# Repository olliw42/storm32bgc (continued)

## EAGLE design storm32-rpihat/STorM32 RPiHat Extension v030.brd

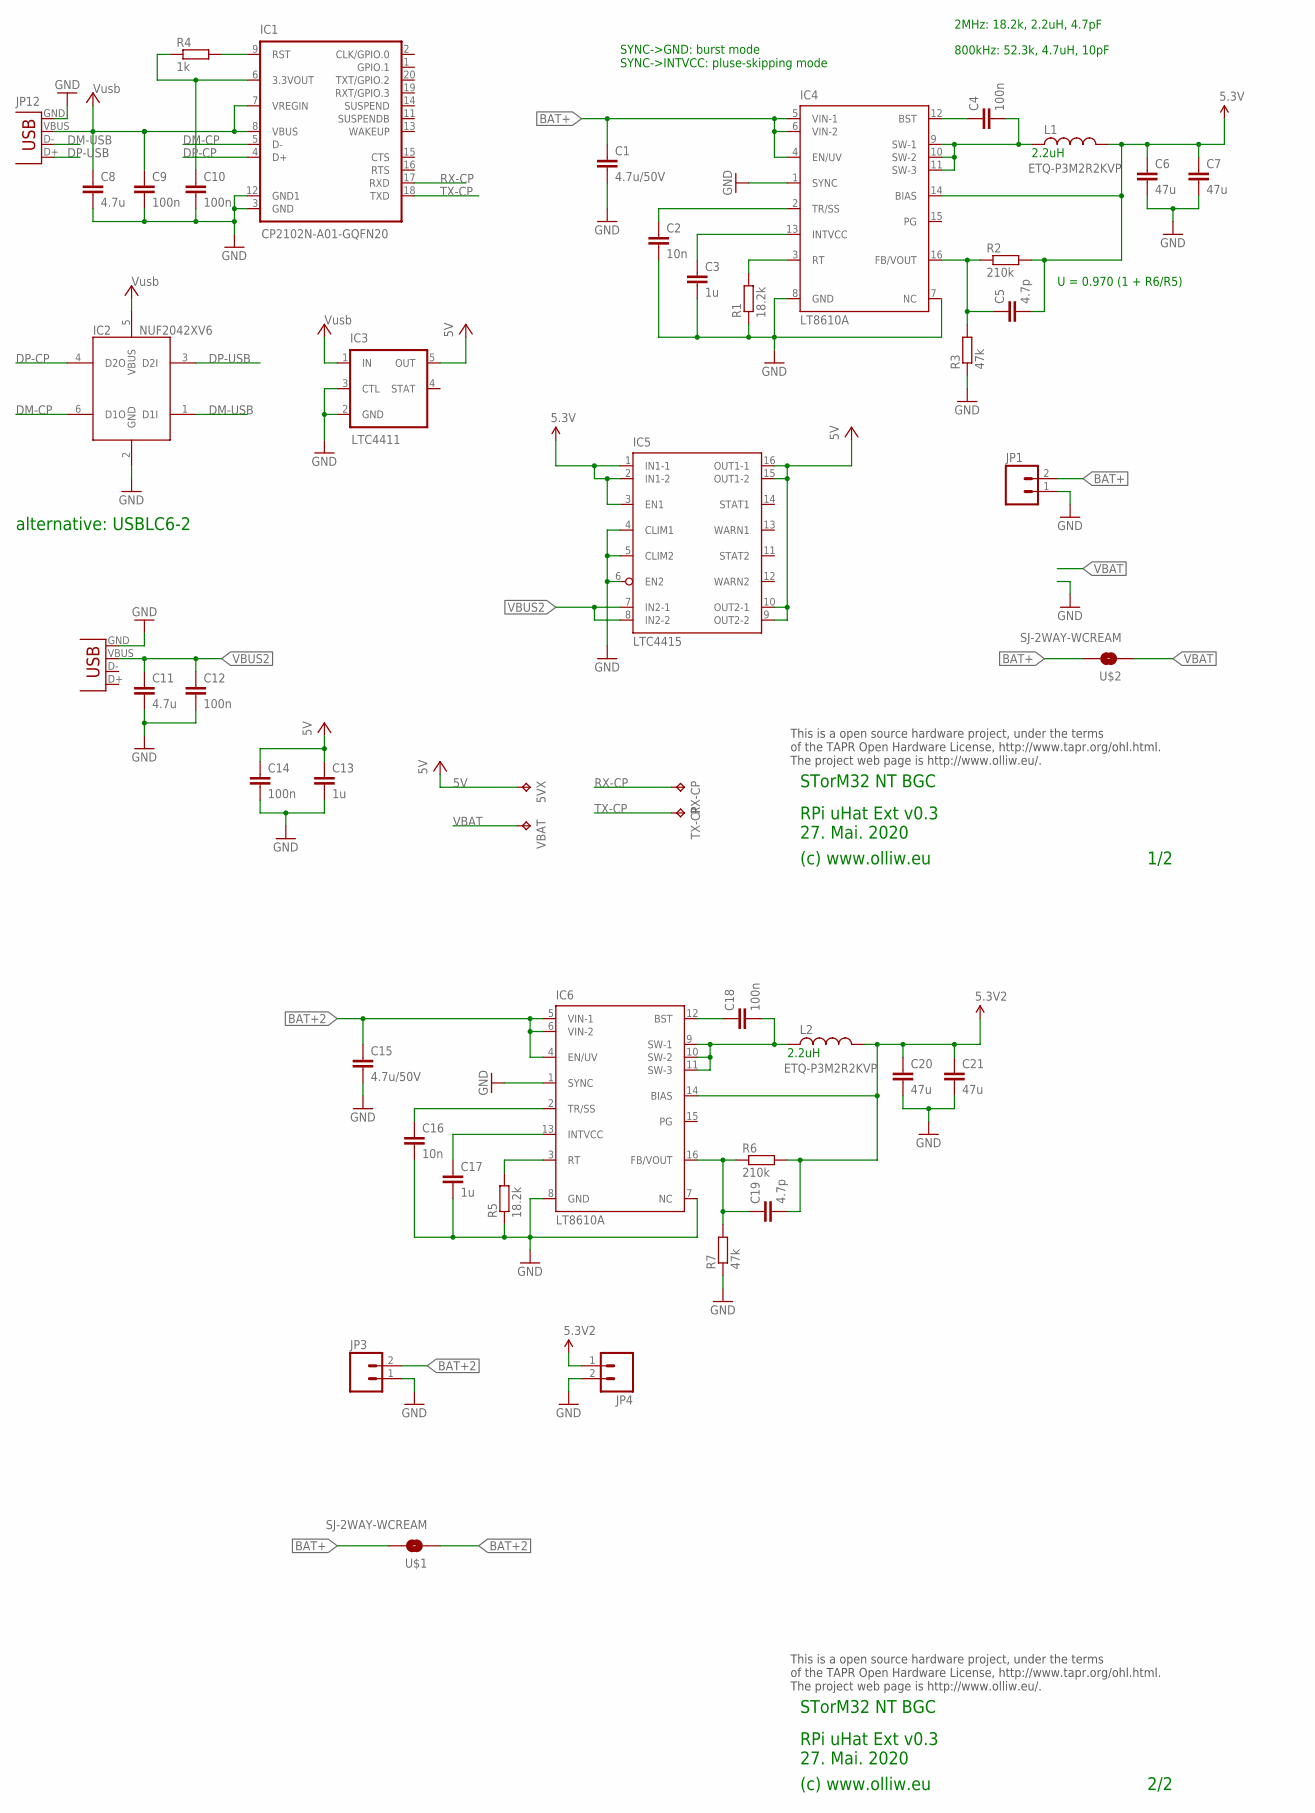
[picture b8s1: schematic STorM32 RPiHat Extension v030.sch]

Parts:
5VX: TPB1,27; B1,27
C1, C15: 4.7u/50V; C1206
C2, C16: 10n; C0603K
C3, C17: 1u; C0603K
C4, C18: 100n; C0603K
C5, C19: 4.7p; C0603K
C6, C7, C20, C21: 47u; C1210
C8, C11: 4.7u; C0603
C9, C10, C12, C14: 100n; C0402
C13: 1u; C0603
IC1: CP2102N-A01-GQFN20; QFN20-CP2102N
IC2: NUF2042XV6; SOT563-6
IC3: LTC4411; SOT23-5-SPARKFUN
IC4, IC6: LT8610A; MSOP16
IC5: LTC4415
JP1, JP3, JP4: M021X02_NO_SILK; 1X02_NO_SILK
L1, L2: ETQ-P3M2R2KVP; L5.4X5.4
R1, R5: 18.2k; R0603
R2, R6: 210k; R0603
R3, R7: 47k; R0603
R4: 1k; R0402
RX-CP: TPB1,27; B1,27
TX-CP: TPB1,27; B1,27
U$1, U$2: SJ-2WAY-WCREAM; SJ-2WAY-BIG-WCREAM
USB, USB1: Amphenol 10118192-0001LF; USB-MICROB
VBAT: TPB1,27; B1,27

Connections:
3.3V-CP2102: C10.1, IC1.6 (3.3VOUT), R4.1
5.3V: C5.2, C6.1, C7.1, IC4.14 (BIAS), IC5.1 (IN1-1), IC5.2 (IN1-2), IC5.3 (EN1), L1.2, R2.2
5.3V2: C19.2, C20.1, C21.1, IC6.14 (BIAS), JP4.1, L2.2, R6.2
5V: 5VX.TP, C13.1, C14.1, IC3.5 (OUT), IC5.9 (OUT2-2), IC5.10 (OUT2-1), IC5.15 (OUT1-2), IC5.16 (OUT1-1)
BAT+: C1.1, IC4.4 (EN/UV), IC4.5 (VIN-1), IC4.6 (VIN-2), JP1.2, U$1.2, U$2.2
BAT+2: C15.1, IC6.4 (EN/UV), IC6.5 (VIN-1), IC6.6 (VIN-2), JP3.2, U$1.1
DM-CP: IC1.5 (D-), IC2.6 (D1O)
DM-USB: IC2.1 (D1I), USB.D-
DP-CP: IC1.4 (D+), IC2.4 (D2O)
DP-USB: IC2.3 (D2I), USB.D+
GND: C1.2, C2.2, C3.2, C6.2, C7.2, C8.2, C9.2, C10.2, C11.2, C12.2, C13.2, C14.2, C15.2, C16.2, C17.2, C20.2, C21.2, IC1.3 (GND), IC1.12 (GND1), IC2.2 (GND), IC3.2 (GND), IC3.3 (CTL), IC4.1 (SYNC), IC4.7 (NC), IC4.8 (GND), IC5.4 (CLIM1), IC5.5 (CLIM2), IC5.6 (EN2), IC6.1 (SYNC), IC6.7 (NC), IC6.8 (GND), JP1.1, JP3.1, JP4.2, R1.1, R3.1, R5.1, R7.1, USB.GND, USB1.GND
unnamed: C19.1, IC6.16 (FB/VOUT), R6.1, R7.2
unnamed: C17.1, IC6.13 (INTVCC)
unnamed: C4.1, IC4.12 (BST)
unnamed: C5.1, IC4.16 (FB/VOUT), R2.1, R3.2
unnamed: C18.1, IC6.12 (BST)
unnamed: IC4.3 (RT), R1.2
unnamed: C3.1, IC4.13 (INTVCC)
unnamed: IC6.3 (RT), R5.2
unnamed: C2.1, IC4.2 (TR/SS)
unnamed: IC1.9 (RST), R4.2
unnamed: C16.1, IC6.2 (TR/SS)
RX-CP: IC1.17 (RXD), RX-CP.TP
SW: C18.2, IC6.9 (SW-1), IC6.10 (SW-2), IC6.11 (SW-3), L2.1
SW1: C4.2, IC4.9 (SW-1), IC4.10 (SW-2), IC4.11 (SW-3), L1.1
TX-CP: IC1.18 (TXD), TX-CP.TP
VBAT: U$2.1, VBAT.TP
VBUS2: C11.1, C12.1, IC5.7 (IN2-1), IC5.8 (IN2-2), USB1.VBUS
VUSB: C8.1, C9.1, IC1.7 (VREGIN), IC1.8 (VBUS), IC2.5 (VBUS), IC3.1 (IN), USB.VBUS

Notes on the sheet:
(c) www.olliw.eu
STorM32 NT BGC
This is a open source hardware project, under the terms of the TAPR Open Hardware License, http://www.tapr.org/ohl.html. The project web page is http://www.olliw.eu/.
RPi uHat Ext v0.3 27. Mai. 2020
1/2
2/2
JP12
alternative: USBLC6-2
2MHz: 18.2k, 2.2uH, 4.7pF
800kHz: 52.3k, 4.7uH, 10pF
U = 0.970 (1 + R6/R5)
SYNC->GND: burst mode SYNC->INTVCC: pluse-skipping mode
2.2uH

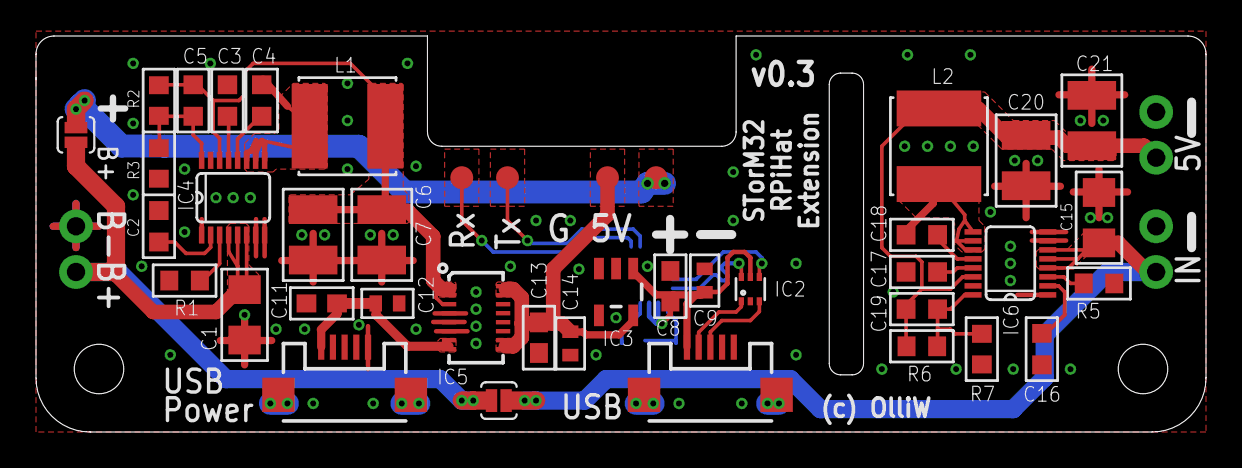
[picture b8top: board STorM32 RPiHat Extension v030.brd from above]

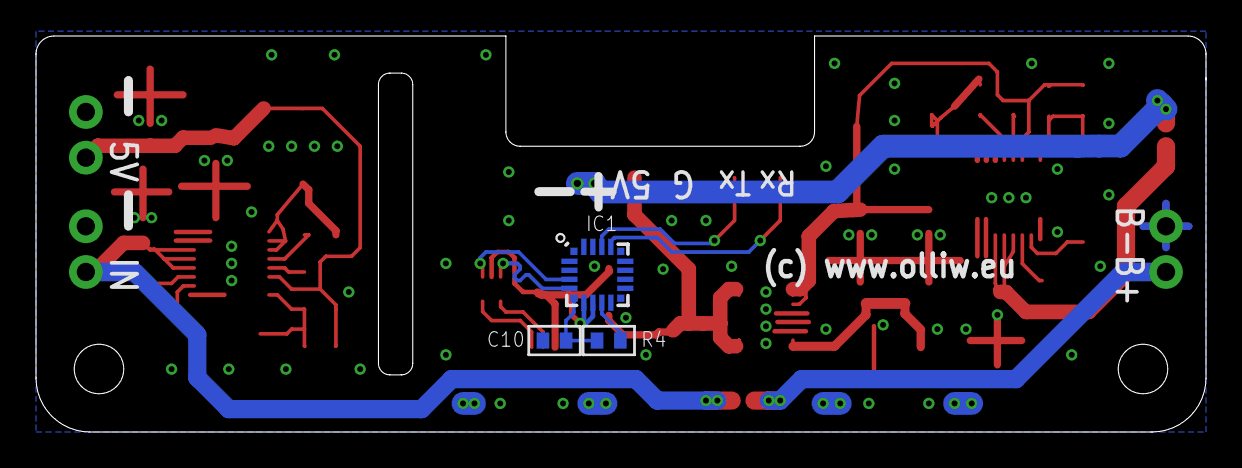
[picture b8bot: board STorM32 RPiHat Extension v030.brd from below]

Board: 2 copper layers, 65.0 x 22.0 mm, 47 parts (3 on the bottom side), 29 nets.

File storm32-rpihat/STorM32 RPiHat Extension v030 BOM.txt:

Stückliste exportiert aus C:/Users/Olli/Documents/GitHub/storm32bgc/storm32-rpihat/STorM32 RPiHat Extension v030.sch am 28.05.2020 11:59

Part  Value                    Device                 Package            Description                TP_SIGNAL_NAME
5VX   TPB1,27                  TPB1,27                B1,27              Test pad                                 
C1    4.7u/50V                 C-EUC1206              C1206              CAPACITOR, European symbol               
C2    10n                      C-EUC0603K             C0603K             CAPACITOR, European symbol               
C3    1u                       C-EUC0603K             C0603K             CAPACITOR, European symbol               
C4    100n                     C-EUC0603K             C0603K             CAPACITOR, European symbol               
C5    4.7p                     C-EUC0603K             C0603K             CAPACITOR, European symbol               
C6    47u                      C-EUC1210              C1210              CAPACITOR, European symbol               
C7    47u                      C-EUC1210              C1210              CAPACITOR, European symbol               
C8    4.7u                     C-EUC0603              C0603              CAPACITOR, European symbol               
C9    100n                     C-EUC0402              C0402              CAPACITOR, European symbol               
C10   100n                     C-EUC0402              C0402              CAPACITOR, European symbol               
C11   4.7u                     C-EUC0603              C0603              CAPACITOR, European symbol               
C12   100n                     C-EUC0402              C0402              CAPACITOR, European symbol               
C13   1u                       C-EUC0603              C0603              CAPACITOR, European symbol               
C14   100n                     C-EUC0402              C0402              CAPACITOR, European symbol               
C15   4.7u/50V                 C-EUC1206              C1206              CAPACITOR, European symbol               
C16   10n                      C-EUC0603K             C0603K             CAPACITOR, European symbol               
C17   1u                       C-EUC0603K             C0603K             CAPACITOR, European symbol               
C18   100n                     C-EUC0603K             C0603K             CAPACITOR, European symbol               
C19   4.7p                     C-EUC0603K             C0603K             CAPACITOR, European symbol               
C20   47u                      C-EUC1210              C1210              CAPACITOR, European symbol               
C21   47u                      C-EUC1210              C1210              CAPACITOR, European symbol               
IC1   CP2102N-A01-GQFN20       CP2102N-QFN20          QFN20-CP2102N                                               
IC2   NUF2042XV6               NUF2042XV6             SOT563-6                                                    
IC3   LTC4411                  LTC411SOT23-5-SPARKFUN SOT23-5-SPARKFUN                                            
IC4   LT8610A                  LT8610                 MSOP16                                                      
IC5   LTC4415                  LTC4415                LTC4415                                                     
IC6   LT8610A                  LT8610                 MSOP16                                                      
JP1                            M021X02_NO_SILK        1X02_NO_SILK       Header 2                                 
JP3                            M021X02_NO_SILK        1X02_NO_SILK       Header 2                                 
JP4                            M021X02_NO_SILK        1X02_NO_SILK       Header 2                                 
L1    ETQ-P3M2R2KVP            LL5.4X5.4              L5.4X5.4                                                    
L2    ETQ-P3M2R2KVP            LL5.4X5.4              L5.4X5.4                                                    
R1    18.2k                    R-EU_R0603             R0603              RESISTOR, European symbol                
R2    210k                     R-EU_R0603             R0603              RESISTOR, European symbol                
R3    47k                      R-EU_R0603             R0603              RESISTOR, European symbol                
R4    1k                       R-EU_R0402             R0402              RESISTOR, European symbol                
R5    18.2k                    R-EU_R0603             R0603              RESISTOR, European symbol                
R6    210k                     R-EU_R0603             R0603              RESISTOR, European symbol                
R7    47k                      R-EU_R0603             R0603              RESISTOR, European symbol                
RX-CP TPB1,27                  TPB1,27                B1,27              Test pad                                 
TX-CP TPB1,27                  TPB1,27                B1,27              Test pad                                 
U$1   SJ-2WAY-WCREAM           SJ-2WAY-WCREAM         SJ-2WAY-BIG-WCREAM                                          
U$2   SJ-2WAY-WCREAM           SJ-2WAY-WCREAM         SJ-2WAY-BIG-WCREAM                                          
USB   Amphenol 10118192-0001LF USB-MICROB             USB-MICROB         USB Connectors                           
USB1  Amphenol 10118192-0001LF USB-MICROB             USB-MICROB         USB Connectors                           
VBAT  TPB1,27                  TPB1,27                B1,27              Test pad

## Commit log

2013-12-02 initial release
2013-12-25 relase update to v1.1
2014-01-04 release v1.1, update with additional gerber files
2014-01-04 replaced by -20131227 zip
2014-02-22 release v1.2 rev1
2014-02-22 folders restructured
2014-03-11 v1.2 rev2
2014-03-16 o323bgc v0.24 relased
2014-03-20 o323bgc v0.25 released
2014-03-21 board v1.3 released
2014-03-21 v1.3 released
2014-05-06 mpu module v009 eagle files added
2014-05-12 o323bgc v0.28 released
2014-05-18 o323bgc v0.29 released
2014-05-28 release firmware v0.31
2014-06-19 release firmware v0.33
2014-06-19 release firmware v0.33 a
2014-10-01 release firmware v0.46
2014-10-11 release firmware v0.51
2014-10-14 added zip
2014-11-28 release firmware v0.56
2015-03-28 release firmware v0.68
2015-04-05 release firmware v0.70
2015-06-06 release firmware v0.79
2015-06-13 release firmware v0.80
2015-06-15 storm32-nt motor&mpu module files uploaded
2015-06-30 nt motor module initial release
2015-07-01 correction
2015-07-10 release nt imu modules
2015-07-16 nt modules upgrade to v1.0
2015-07-16 nt modules updgrade to v1.0
2015-08-13 release nt imu mini 9250 & breakout modules
2015-08-19 release nt motor v11, deprecate nt motor v10 & imu v10 mpu6000
2016-01-12 release firmware v0.90 (wo NTLoggerTool)
2016-01-12 firmware release v0.90
2016-03-18 release imu modules v11
2016-03-19 firmware release v0.96
2016-03-19 blackbox explorer readme added
2016-03-28 release firmware v2.00
2016-03-30 release firmware v2.01, v2.00 removed
2016-04-08 release firmware v2.02
2016-04-12 release v2.03
2016-08-01 test
2016-08-02 betacopter 3.4rc1 011
2016-08-04 betacopter v013
2016-08-06 betacopter 34dev v015
2016-08-08 betacopter 34rc2 v017
2016-09-10 betacopter34rc4-v019
2016-09-15 release betacopter34rc5-v20
2016-09-26 release betacopter34rc5-v021
2016-12-30 release firmware v2.20
2017-01-12 release v2.x hardware
2017-03-09 release TSTorM32 motor modules v24E
2017-05-20 main board v2.4 deprecated
2017-07-30 release firmware 2.30
2017-08-03 rerelease v2.30
2017-08-18 betacopter36dev-v003
2017-08-19 betacopter 36dev v005
2017-11-11 release board v3.3, motor v2.5E, oled, esp
2017-11-12 v33m BOM added
2017-11-12 v33m BOM improved
2017-12-27 release NT imu v2.11, NT encoder motor v2.51E, display v1.3
2018-02-04 release nt logger v1.2
2018-02-07 clarify content of betacopter zip
2018-02-07 betacopter readme.md
2018-02-19 readme.md
2018-02-22 release NT Logger v1.3
2018-02-25 release betacopter 3.6-dev v006
2018-02-25 readme bump
2018-05-29 firmware folder cleaned up
2018-06-02 release v2.38e
2018-06-21 release betacopter-36dev-v008-rc1
2018-06-22 readme dump
2018-06-30 release firmware v2.39e
2018-06-30 release betacopter 36-dev v008
2018-07-21 release betacopter 3.6.0-rc6 v009s
2018-07-22 release betacopter 3.6dev v009
2018-07-26 release betacopter 3.6.0-rc6 v010s
2018-08-02 release betacopter 3.6.0-rc7 v011s
2018-08-07 release firmware v2.40
2018-09-10 T-STorM32 group buy stuff uploaded
2018-09-10 readme update
2018-10-03 release betacopter36dev-v012
2018-11-04 release betacopter 3.6.0-v013s, 3.6.0-v013u
2018-11-10 release betacopter 3.6.1 v0.14u
2018-11-15 release betacopter 3.6.1 v0.15u
2019-10-12 release firmware v2.43e
2019-10-27 release firmware v2.44e
2019-11-03 release firmware v2.45e
2019-11-24 release firmware v2.46e
2019-11-24 storm32 micro release: bgc v3.33i, motor v2.52E, usbpower v0.20
2019-11-24 readme updated
2019-12-01 release firnware v2.47e
2019-12-22 release firmware v2.48e
2020-01-01 release firmware v2.49e
2020-01-13 add ntloggertool ref
2020-01-18 release firmware v2.50e
2020-03-24 release firmware v2.51e
2020-04-20 release official firmware v2.52
2020-05-17 release official firmware v2.53
2020-05-23 release STorM32 main board v3.33i
2020-05-24 release STorM32 Mirco Motor Triple Board v0.20
2020-05-28 release STorM32 Micro Motor Triple Board v0.30
2020-05-28 release STorM32 RPi Hat v0.60, extension board v0.30
2020-06-05 release STorM32 Micro Logger Board v1.32
2020-06-05 readme
2020-06-06 release firmware v2.54e
2020-08-18 release firmware v2.56e
2020-09-17 create LICENSE
2020-09-17 edit LICENSE
2020-11-15 add STorM32 C library
2020-11-15 update to 15. Nov. 2020
2020-11-17 make folder old, move stuff into it
2020-11-17 some clean ups
2020-11-29 add storm32.xml, v 25. Nov. 2020
2020-11-29 add rudimentary STorM32 Python library
2020-12-02 release firmware v2.57e
2020-12-02 correct zip file name of v2.57e
2020-12-08 storm32.xml some cleanups
2021-09-08 release firmware v2.59e
2022-11-01 release firmware v2.62g
2022-11-02 release firmware v2.62i
2022-12-09 add mavlink events json
2022-12-31 remove v2.62i
2023-01-09 release firmware v2.64e
2023-01-21 release firmware 2.65e
2023-04-16 release alpha firmware v2.67b
2023-10-02 release firmware v2.67e
2023-10-21 firmware v2.67e, correct ntmotor triple firmware hex file
2023-10-29 release STorM32 NT Imu board v4.2 G4
2024-01-10 release firmware v2.69e
2024-01-10 release STorM32 NT Logger module v2.2 G4
2024-01-19 release STorM32 v4.1 board, design by KrattWorks
2024-01-22 add v4.1 board pins
2024-03-26 add gerber files for storm32-nt-imu-v42-g4
2024-03-27 Gerber files for storm32-nt-imu-v42-g4 and storm32-nt-logger-v2x-g4
2024-07-06 NTLoggerTool scripts
2024-07-06 copyright notice, sheband, tidy
2024-07-06 remove mavlink folder, add few more readmes
2025-05-02 release firmware v2.70e
2025-05-02 release STorM32 NT Motor module v4.2EC G4
2025-05-07 update of STorM32 NT Motor module v4.2EC G4, few corrections&updates (thx to qvertigo)
2025-05-19 release firmware v2.71e
2025-06-14 release firmware v2.72e
